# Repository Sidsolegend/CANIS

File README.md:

# CANIS

A small robot that gives my dog treats for calm behaviour.

*The current robot: a Meccano frame, an ESP32 and an Arduino on a breadboard, an ESP32-CAM on top, and three ultrasonic sensors at the front.*

## Why I built it

My Goldendoodle, Shifu, is afraid of moving objects. He also barks for attention, and he gets into trouble when he is bored. A robot is the worst possible thing to put in front of a dog like that, so the design starts from that constraint. CANIS never punishes him and never drives towards him. It rewards him when he settles, when he leaves a spot he shouldn't be in, or when he stops barking. Any motion is something I introduce slowly and switch off by default.

## What it does

- **Three modes.** `PLACE` (the default) gives a treat when Shifu settles on his mat. `GUARD` stays at a spot, gives a short buzzer cue when he comes near, and rewards him for leaving. `PLAY` wanders the room, gives a treat when it sees him, then backs away so he can follow. It never moves towards him.
- **Dog detection.** A YOLO11n model on a Raspberry Pi 5 finds the dog in the camera image and estimates his bearing and distance. The camera is either the Pi's own or an ESP32-CAM streaming over WiFi.
- **Bark detection.** A DJI Mic 3 connects to the Pi over Bluetooth. After a bark, the robot waits for five seconds of quiet and then drops a treat. A dead or muted microphone is treated as "not quiet", so a failure never rewards the wrong thing.
- **Treat dispenser.** A servo-driven gate on an Arduino Uno, with a short tone before each treat so the sound predicts food. There is a cooldown between treats and a daily cap.
- **Dashboard.** A Flask app on the Pi shows live state, keeps an event log and exports CSV files for the study.
- **Safety layer.** The Arduino stops the motors if it hasn't heard from the ESP32 for one second, so a crashed program or a loose wire ends with a stopped robot. A single exposure setting decides how much motion is allowed at all. It starts at zero.
- **Closed-loop drive.** The N20 motors have encoders (754 counts per wheel turn, about 0.18 mm per count). A per-wheel speed controller matches the two wheels, and a control-barrier-function safety filter sits between the controller and the motors: it only removes motion towards Shifu, never adds it, so the robot never closes inside a 60 cm comfort distance. Top speed is capped at 0.35 m/s. Both have been run on the robot.

## How it was built

| | |
|---|---|
|  | **1. Prototype.** The first rolling version: a Meccano frame, a Raspberry Pi 5, and geared motors with large wheels. It proved the vision and treat loop before I committed to a design. |
|  | **2. CAD, version 1.** A fully printable two-tier enclosure, modelled in OpenSCAD for a Bambu P1S. |
|  | **3. CAD, version 2.** A flap-gate dispenser and a shell that closes around the boards. |
|  | **4. CAD, version 3.** A reshaped shell, which I never finished as a full set of parts. |
|  | **5. CAD, version 4.** The last printable design, with the deck and shell checked for slicing. |
|  | **6. What I actually run.** I stopped printing the shell and went back to the metal frame. The dispenser housing is the main printed part. The old motors were replaced with small N20 encoder motors, and the front sensor, ESP32-CAM and bark detection were added. |

The longer story, including what went wrong, is in [docs/BUILD_STORY.md](docs/BUILD_STORY.md).

## Architecture

```mermaid
flowchart LR
    subgraph Pi["Raspberry Pi 5 (eyes, ears, dashboard)"]
        V["YOLO dog detection"]
        B["Bark detector (DJI Mic 3)"]
        D["Flask dashboard and event log"]
    end
    subgraph ESP["ESP32 (brain)"]
        S["Ultrasonic sensors"]
        M["State machine and reward policy"]
    end
    subgraph UNO["Arduino Uno (limbs)"]
        W["1 s motion watchdog"]
        MOT["L298N and motors"]
        G["Servo gate and buzzer"]
    end
    V --> D
    B --> D
    D <-- WiFi --> M
    S --> M
    M -- serial --> UNO
```

Each processor does one kind of job, and each one fails on its own. The Uno is deliberately simple. It runs the motors and the gate and stops the wheels when commands stop arriving. The ESP32 reads the sensors and decides what to do. The Pi does the heavy work (vision, audio, logging). More in [docs/ARCHITECTURE.md](docs/ARCHITECTURE.md) and [docs/TECHNICAL_OVERVIEW.md](docs/TECHNICAL_OVERVIEW.md).

## Hardware

| Part | Used for |
|---|---|
| Raspberry Pi 5 | vision, bark detection, dashboard |
| ESP32 DevKit V1 | sensors, state machine, WiFi |
| Arduino Uno | dispenser, motors, buzzer |
| ESP32-CAM (AI-Thinker, OV2640) | camera on the robot |
| L298N driver, 2 x GA12-N20 150 rpm encoder motors, 43 mm wheels | drive |
| 2 x HC-SR04 and 1 x JSN-SR04M-2 | left, right and front distance |
| SG90 servo, small buzzer | treat gate and the marker tone |
| DJI Mic 3 | bark detection, over Bluetooth |
| 6 x AA pack for the motors, a small USB power bank for the electronics | power |
| Meccano frame, printed dispenser housing, castor | chassis |

Wiring, pin tables and power notes: [hardware/WIRING.md](hardware/WIRING.md). Bring-up tests: [hardware/TESTING.md](hardware/TESTING.md).

## Repository layout

```
CANIS_Core/              ESP32 firmware (brain)
Treat_Dispenser_CANIS/   Arduino firmware (dispenser, motors, buzzer)
canis_config.h           every tunable value for the firmware, in one place
vision/                  YOLO dog detection (Pi)
audio/                   bark detection (Pi)
dashboard/               Flask dashboard and event log (Pi)
control/                 closed-loop controller and safety filter
study/                   study protocol and the analysis script
tests/                   118 tests, no hardware needed
hardware/                wiring, bring-up guides, CAD, STL files
docs/                    architecture, safety, interfaces, build story, known issues
prototypes/              early test sketches from before the current firmware
```

## Running it

Run the tests (no hardware needed):

```bash
pip install pytest numpy -r dashboard/requirements.txt
python3 -m pytest tests/ -q
```

Run the dashboard on the Pi:

```bash
cd dashboard
pip install -r requirements.txt
export CANIS_TOKEN=$(openssl rand -hex 16)   # shared secret, also set in arduino_secrets.h
python3 app.py                                # listens on port 5000
```

Flash the firmware: copy `CANIS_Core/arduino_secrets.h.example` to `CANIS_Core/arduino_secrets.h` and fill in your WiFi details, the Pi's address and the token. That file is git-ignored. Then flash `CANIS_Core` to the ESP32 (115200 baud) and `Treat_Dispenser_CANIS` to the Uno (9600 baud).

Start vision and bark detection on the Pi. Setup commands are at the top of each file.

```bash
python3 vision/detect_yolo.py --zone kitchen
python3 audio/detect_bark.py --bt-mac <microphone address>
```

## Status

What has been run:
- The full loop, camera to detection to dashboard to ESP32 to treat, works on the bench.
- The bark loop works end to end: a bark, five seconds of quiet, then a treat. In the live test there were no false positives.
- Encoder test: 754 counts per wheel turn, measured over 10 hand turns with 4x decoding. That fits a 3-pulse encoder on a 63:1 gearbox (3 x 63 x 4 = 756).
- Mobile drive with the closed-loop controller and the safety filter has been tested on the robot, with Shifu in the room.
- 118 automated tests pass.

The trial with Shifu:
- Week 1 was stationary acclimation: treats on, no motion, sessions growing from 15 to 60 minutes a day. He was scared of the robot the first time and got used to it over these sessions.
- Week 2 turned on mobile drive and `GUARD`. Over that week, treats earned rose by about 25% from day 1 to day 7.
- This is one dog with no control, so I can't rule out that he simply got used to the robot, and treats are counted when they are sent, not when they drop (see below). The raw session logs are in my notes, not in this repo yet.

Not finished yet:
- The repo config still has the old wheel values and `CANIS_MOBILE_ENABLED` set to 0. The robot runs with the measured values; the config here will be updated.
- Treat confirmation from the dispenser is designed but not wired (the 5 V to 3.3 V return line needs a divider), so treats are counted on send.
- The next step is a pre-registered study with a proper baseline, following [study/STUDY_PROTOCOL.md](study/STUDY_PROTOCOL.md).

Known problems and limits are listed in [docs/KNOWN_ISSUES.md](docs/KNOWN_ISSUES.md).

## About the code

I built and wired the robot, ran the bench tests and decided how it should behave around Shifu. AI coding assistants helped write and review parts of the software and the documentation.

## License

MIT. See [LICENSE](LICENSE).

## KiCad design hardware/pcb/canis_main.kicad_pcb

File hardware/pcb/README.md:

# CANIS main board (v1, untested)

One 100 x 90 mm, 2-layer, all through-hole board that replaces the Arduino Uno, the breadboard and the loose wiring. The L298N module stays off-board and is wired to it. The ESP32 DevKit plugs into two 1x15 sockets. Everything else is on the board.

Status: DRC clean (0 errors, 0 unconnected, only silkscreen-overlap warnings) in KiCad, and `check_netlist.py` passes. **Never fabricated or powered.** Treat the checklist below as required before ordering.

## What is on it

| Block | Parts | Notes |
|---|---|---|
| Logic | ATmega328P-PU in a DIP-28 socket, 16 MHz crystal, 2 x 22p, 10k reset, reset button | Same pins as the Uno, so `Treat_Dispenser_CANIS.ino` runs unchanged (D2 button, D3/D4/D7/D8/D12/D5 motors, D6 buzzer, D9 servo, D10/D11 link, A0 beam) |
| Motors | 1x6 header (ENA IN1 IN2 IN3 IN4 ENB, same order as the module's own header) and a 2-pin screw terminal (12V, GND) for your existing red L298N module | Use female-female jumpers for the 6 control wires. Motor wires go straight to the module's own OUT terminals. Leave the module's 5V jumper on; its 5V terminal is not connected to this board |
| Power | LM2596T-5.0 buck + 33uH + 1N5822 + 470u in/out, 1N5822 reverse-polarity diode on the battery | Battery in goes to the L298 (VMOT) and the buck. 1N5819 from 5V to ESP32 VIN so USB cannot back-feed the buck |
| Sensors | 3 x 4-pin (5V, TRIG, ECHO, GND) with 1k series on each ECHO, 2 x 4-pin encoder (3V3, GND, A, B) with 10k pull-ups, I2C header | Pin map is `canis_config.h` and the `.ino` files, not the old WIRING.md |
| Outputs | servo (3-pin), buzzer (2-pin with 220R), button (2-pin), beam (3-pin), ESP32-CAM 5V/GND | |
| Programming | ICSP 2x3, UART 4-pin (GND, DTR, TX, RX) with auto-reset cap | |
| Link | ESP32 GPIO13 to ATmega D10 direct; ATmega D11 to ESP32 GPIO4 through 1k + 2.2k divider | This is the dispense-ACK return line, so `CANIS_USE_DISPENSE_ACK` can be 1 on this board |

ESP32 pins: US trig/echo 27/25 (centre), 32/34 (left), 14/35 (right); encoders L 33/26, R 36/39; link 13 and 4; I2C 21/22.

## Before you order (check these)

1. **DevKit pinout and row spacing.** The board assumes a 30-pin DevKit V1 with rows 25.4 mm apart and USB at the top edge of the board. Measure yours with calipers (`ESP_AX`/`ESP_BX` in `gen_pcb.py`) and check the pin order against its silkscreen.
2. **L298N module header order.** The 6-pin control header is wired ENA, IN1, IN2, IN3, IN4, ENB, top to bottom as on the usual red module. Check yours against its silkscreen. Print `canis_main_testprint_1to1.pdf` at 100% and drop the real parts on it (LM2596, terminal blocks, crystal, DevKit) before paying for boards.
3. **LM2596 pinout** is the standard TO-220-5 (1 Vin, 2 Out, 3 GND, 4 FB, 5 ON/OFF to GND). Set nothing, it is the fixed 5.0 V part. Measure 5 V on the board with nothing plugged in before adding the ESP32 or the ATmega.
4. **Motor drop.** The L298N module still drops about 2 V, plus 0.4 V in the reverse diode, so the N20 motors see roughly 7 V from a 9.9 V pack. Same as the module today, minus the diode.
5. **Antenna.** There is a copper keep-out under the DevKit's antenna end. It does not fix the weak WiFi (-72 to -84 dBm in the notes).

## Bring-up order

1. Solder power only (J3, D1, C1, C3, U2, D2, L1, C2). Battery in, meter the 5V rail. Mind the polarity: the lower terminal of J3 is +.
2. Add the ATmega socket parts, crystal, caps, reset. The chip needs the Uno bootloader once: burn it over ICSP (a USBasp or another Uno as ISP), or buy it pre-flashed. After that the UART header uploads the sketch with auto-reset. Do not power the board from the programmer's 5V at the same time as the battery.
3. Add the headers and terminals, then wire the L298N module. Plug the DevKit in last.

GND pads are connected solid to the pour (thermal spokes kept landing on islands), so use a hot iron and flux.

## Files

- `gen_pcb.py` builds the board; `route.py` autoroutes with Freerouting (jar not in the repo, Java 21+) and pours GND; `build.sh` regenerates and renders.
- `check_netlist.py` re-checks the board's pins against the firmware sources (run it after any change).
- `canis_main.kicad_pcb`, `canis_main.kicad_pro`: open in KiCad. There is no schematic file; the netlist lives in `gen_pcb.py` (net names are the signal names above).
- `gerbers/` and `canis_main_gerbers.zip`: fab files (Gerber + Excellon).
- `canis_main_bom.csv`, `canis_main_preview.png`, `canis_main_testprint_1to1.pdf`.

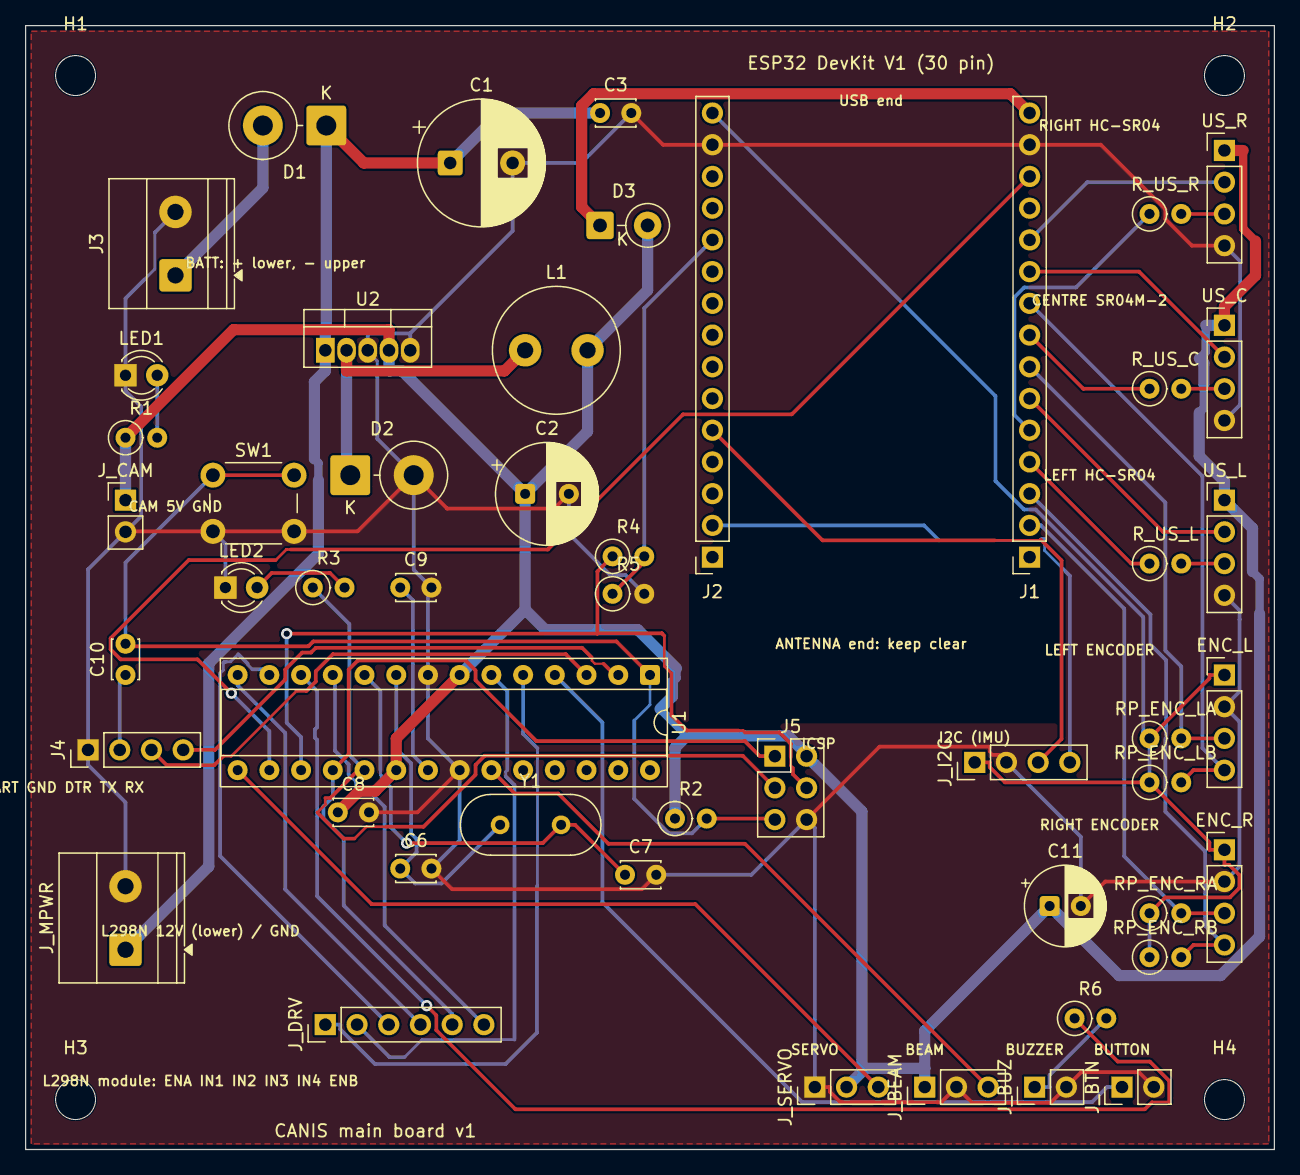
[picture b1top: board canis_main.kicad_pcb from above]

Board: 2 copper layers, 100.0 x 90.0 mm, 54 parts (0 on the bottom side), 46 nets.

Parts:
C1: 470u 25V; CP_Radial_D10.0mm_P5.00mm
C2: 470u 16V (5V out); CP_Radial_D8.0mm_P3.50mm
C3: 100n; C_Disc_D3.0mm_W2.0mm_P2.50mm
C6, C7: 22p; C_Disc_D3.0mm_W2.0mm_P2.50mm
C8: 100n VCC; C_Disc_D3.0mm_W2.0mm_P2.50mm
C9: 100n AREF; C_Disc_D3.0mm_W2.0mm_P2.50mm
C10: 100n DTR; C_Disc_D3.0mm_W2.0mm_P2.50mm
C11: 220u servo; CP_Radial_D6.3mm_P2.50mm
D1: 1N5822 reverse protect; D_DO-201AD_P5.08mm_Vertical_CathodeUp
D2: 1N5822 buck; D_DO-201AD_P5.08mm_Vertical_CathodeUp
D3: 1N5819 5V->VIN; D_DO-41_SOD81_P3.81mm_Vertical_CathodeUp
ENC_L: LEFT ENCODER 3V3 GND A B; PinHeader_1x04_P2.54mm_Vertical
ENC_R: RIGHT ENCODER 3V3 GND A B; PinHeader_1x04_P2.54mm_Vertical
H1, H2, H3, H4: M3; MountingHole_3.2mm_M3
J1: ESP32 DevKit left header (EN..VIN); PinSocket_1x15_P2.54mm_Vertical
J2: ESP32 DevKit right header (D23..3V3); PinSocket_1x15_P2.54mm_Vertical
J3: BATT 6xAA; TerminalBlock_Phoenix_MKDS-1,5-2-5.08_1x02_P5.08mm_Horizont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
J4: UART (FTDI/CP2102) GND DTR TXD RXD; PinHeader_1x04_P2.54mm_Vertical
J5: ICSP; PinHeader_2x03_P2.54mm_Vertical
J_BEAM: BEAM 5V GND OUT; PinHeader_1x03_P2.54mm_Vertical
J_BTN: BUTTON D2 GND; PinHeader_1x02_P2.54mm_Vertical
J_BUZ: BUZZER SIG GND; PinHeader_1x02_P2.54mm_Vertical
J_CAM: ESP32-CAM 5V GND; PinHeader_1x02_P2.54mm_Vertical
J_DRV: TO L298N module: ENA IN1 IN2 IN3 IN4 ENB; PinHeader_1x06_P2.54mm_Vertical
J_I2C: I2C 3V3 GND SDA SCL; PinHeader_1x04_P2.54mm_Vertical
J_MPWR: TO L298N 12V / GND; TerminalBlock_Phoenix_MKDS-1,5-2-5.08_1x02_P5.08mm_Horizont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
J_SERVO: SERVO GND 5V SIG; PinHeader_1x03_P2.54mm_Vertical
L1: 33uH 3A; L_Radial_D10.0mm_P5.00mm_Fastron_07P
LED1: green 5V; LED_D3.0mm
LED2: amber D13; LED_D3.0mm
R1, R3, R4: 1k; R_Axial_DIN0207_L6.3mm_D2.5mm_P2.54mm_Vertical
R2: 10k reset; R_Axial_DIN0207_L6.3mm_D2.5mm_P2.54mm_Vertical
R5: 2.2k; R_Axial_DIN0207_L6.3mm_D2.5mm_P2.54mm_Vertical
R6: 220; R_Axial_DIN0207_L6.3mm_D2.5mm_P2.54mm_Vertical
RP_ENC_LA: 10k; R_Axial_DIN0207_L6.3mm_D2.5mm_P2.54mm_Vertical
RP_ENC_LB: 10k; R_Axial_DIN0207_L6.3mm_D2.5mm_P2.54mm_Vertical
RP_ENC_RA: 10k; R_Axial_DIN0207_L6.3mm_D2.5mm_P2.54mm_Vertical
RP_ENC_RB: 10k; R_Axial_DIN0207_L6.3mm_D2.5mm_P2.54mm_Vertical
R_US_C: 1k; R_Axial_DIN0207_L6.3mm_D2.5mm_P2.54mm_Vertical
R_US_L: 1k; R_Axial_DIN0207_L6.3mm_D2.5mm_P2.54mm_Vertical
R_US_R: 1k; R_Axial_DIN0207_L6.3mm_D2.5mm_P2.54mm_Vertical
SW1: RESET; SW_PUSH_6mm
U1: ATmega328P-PU (Uno bootloader); DIP-28_W7.62mm_Socket
U2: LM2596T-5.0; TO-220-5_Vertical
US_C: CENTRE SR04M-2 5V TRIG ECHO GND; PinHeader_1x04_P2.54mm_Vertical
US_L: LEFT HC-SR04 5V TRIG ECHO GND; PinHeader_1x04_P2.54mm_Vertical
US_R: RIGHT HC-SR04 5V TRIG ECHO GND; PinHeader_1x04_P2.54mm_Vertical
Y1: 16 MHz; Crystal_HC49-4H_Vertical

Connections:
3V3: ENC_L.1, ENC_R.1, J2.15, J_I2C.1, RP_ENC_LA.1, RP_ENC_LB.1, RP_ENC_RA.1, RP_ENC_RB.1
5V: C2.1, C8.1, C11.1, D3.2, J5.2, J_BEAM.1, J_CAM.1, J_SERVO.2, L1.2, R1.1, R2.1, U1.7, U1.20, U2.4, US_C.1, US_L.1, US_R.1
AREF: C9.1, U1.21
BEAM: J_BEAM.3, U1.23
BTN: J_BTN.1, U1.4
BUZ: J_BUZ.1, R6.2
BUZ_RAW: R6.1, U1.12
D0_RX: J4.4, U1.2
D1_TX: J4.3, U1.3
D13_LED: J5.3, R3.1, U1.19
DTR: C10.1, J4.2
ENC_L_A: ENC_L.3, J1.7, RP_ENC_LA.2
ENC_L_B: ENC_L.4, J1.9, RP_ENC_LB.2
ENC_R_A: ENC_R.3, J1.2, RP_ENC_RA.2
ENC_R_B: ENC_R.4, J1.3, RP_ENC_RB.2
GND: C1.2, C2.2, C3.2, C6.2, C7.2, C8.2, C9.2, C11.2, D2.2, ENC_L.2, ENC_R.2, J1.14, J2.14, J3.2, J4.1, J5.6, J_BEAM.2, J_BTN.2, J_BUZ.2, J_CAM.2, J_I2C.2, J_MPWR.2, J_SERVO.1, LED1.1, LED2.1, R5.2, SW1.2, U1.8, U1.22, U2.3, U2.5, US_C.4, US_L.4, US_R.4
I2C_SCL: J2.2, J_I2C.4
I2C_SDA: J2.5, J_I2C.3
LED5: LED1.2, R1.2
LED13: LED2.2, R3.2
LINK_RX_AT: J1.13, U1.16
LINK_TX_AT: J5.4, R4.1, U1.17
LINK_TX_DIV: J2.11, R4.2, R5.1
M_ENA: J_DRV.1, U1.5
M_ENB: J_DRV.6, U1.11
M_IN1: J_DRV.2, U1.6
M_IN2: J_DRV.3, U1.13
M_IN3: J_DRV.4, U1.14
M_IN4: J5.1, J_DRV.5, U1.18
RESET: C10.2, J5.5, R2.2, SW1.1, U1.1
SERVO: J_SERVO.3, U1.15
SW: D2.1, L1.1, U2.2
US_C_ECHO: J1.8, R_US_C.1
US_C_ECHO_RAW: R_US_C.2, US_C.3
US_C_TRIG: J1.10, US_C.2
US_L_ECHO: J1.4, R_US_L.1
US_L_ECHO_RAW: R_US_L.2, US_L.3
US_L_TRIG: J1.6, US_L.2
US_R_ECHO: J1.5, R_US_R.1
US_R_ECHO_RAW: R_US_R.2, US_R.3
US_R_TRIG: J1.11, US_R.2
VBAT: D1.2, J3.1
VIN_ESP: D3.1, J1.15
VMOT: C1.1, C3.1, D1.1, J_MPWR.1, U2.1
XTAL1: C6.1, U1.9, Y1.1
XTAL2: C7.1, U1.10, Y1.2

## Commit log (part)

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2026-06-25 Initial commit: CANIS conditioning robot
    Working closed loop: sensors -> state machine -> dispense + buzzer cue,
    with live ESP32->Pi dashboard. Credentials kept out of git via
    arduino_secrets.h (gitignored).
    Subsystems:
    - CANIS_Core: integrated ESP32 brain (PIR + ultrasonic, arousal state
    machine, treat dispense, CORRECTION buzzer cue, reward cooldown/cap,
2026-06-25 Docs: update setup for arduino_secrets.h credential flow
2026-06-25 Add systemd service for the dashboard; make Flask debug opt-in (CANIS_DEBUG)
2026-06-25 Docs: Pi prepped for vision (opencv-contrib + ArUco); dashboard auto-start
2026-06-25 Add Pi->ESP32 vision command channel (/detect, /command) + ArUco detection script
    - Flask: /detect (vision posts zone) + /command (ESP32 polls); TTL-based staleness
    - CANIS_Core: polls /command, folds vision detections into arousal drive, shares Pi back-off
    - vision/detect.py: ArUco marker detection -> POST zone, with --test mode (no camera needed)
    - docs: refreshed repo layout + Phase 6 status
2026-06-25 Harden CANIS_Core: fixed-buffer visionZone (no heap churn) + rollover-safe backoff
2026-06-25 Reward tuning: gate sustained-calm reward until warm-up; calm interval (30s) >= cooldown (20s)
2026-06-25 Add hardware/WIRING.md (pinout + power architecture + L298N plan); refresh README
    - New hardware/WIRING.md: every pin, the ECHO protection, power architecture
    (USB now, battery/buck later), and the planned L298N->Arduino wiring
    - README: rate-driven arousal description (was stale +25 bump), CANIS_Core as
    the main sketch, hardware/power links, refreshed phase status
2026-06-29 Add parametric 3D-printed chassis, product shell & mounts (hardware/cad)
    Parametric OpenSCAD model (canis.scad) for the hybrid CANIS build, sized for
    a Bambu P1S in PLA. Seven printable parts + STLs + preview renders.
    - Deck (230x175): ribbed load-bearing plate with a real, collision-free home for
    every component — Pi 5 cradle, board pads (Arduino, ESP32, L298N, LM2596 buck),
    breadboard pad, dispenser/motor/castor/shell holes, cable routing.
    - Shell: product enclosure with a "paw" front that actually mounts the sensors
2026-06-29 Fix layout overlaps: re-pack deck (240x185), separate servo tower, relocate shell bosses
    - Deck 230x175 -> 240x185; re-pack so NO pad/cradle/dispenser/boss overlaps.
    Breadboard pad no longer intersects the Pi cradle.
    - Dispenser: servo tower moved BEHIND the throat with an asymmetric base, so it
    no longer cuts into the funnel/throat; shell hopper opening is now an oval that
    clears funnel + tower.
    - Shell screw bosses relocated to verified-clear perimeter gaps (were landing
2026-06-29 Fix deck ribs through throat, declutter paw mounts, clean dispenser; deck 248x190
    Geometry bugs caught by per-part close-up renders:
    - Deck: a stiffening rib ran under the throat (would block treats). Ribs moved
    clear of the throat AND all holes/slots now cut FULL depth (through ribs), so
    the throat, cable slots and screw holes are never blocked.
    - Deck mounts: boards on 4 open standoffs (deck stays open underneath), breadboard
    on a perimeter lip (open centre) — nothing covers the deck or its holes.
2026-06-29 Rebuild as clean two-tier model (205x165): lower deck + upper shelf, modular sensor plate
    Fresh rebuild after the single-tier file accumulated geometry bugs. Simpler,
    smaller, verified part-by-part:
    - Two tiers: lower deck (Pi 5, L298N, buck, motors, castor, dispenser) + upper
    shelf on 4 standoffs (Arduino, breadboard, ESP32). Shelf has a rear notch so
    the dispenser funnel passes up through it.
    - No underside ribs (4mm plate + skirt) -> nothing crosses the throat/holes.
2026-06-29 Clean funnel + separate servo bracket, readable logo, single combined STL
    - Dispenser is now a CLEAN funnel only (round throat + 3 feet); the servo moved
    to its own `servo_bracket` part beside the funnel, enclosed under the shell.
    No more tab/notch fighting the throat.
    - Shell hopper opening simplified to the funnel circle; CANIS logo deepened so
    it's clearly readable on the rear.
    - Shelf wire holes tidied into a clean column.
2026-06-29 Push CANIS logo down clear of the hopper opening (now fully readable)
2026-06-29 Rebuild dispenser as a working rotating-disc mechanism (servo + disc + chute)
    Replaces the non-functional funnel+gate. Now an actual mechanism:
    - dispenser = round housing + funnel; the SG90 stands upright INSIDE (shaft up),
    the disc sits on its shaft.
    - disc = one metering pocket + centre horn socket; fills under the funnel inlet
    (-x), rotates 180deg, drops one kibble through the +x exit.
    - exit drops through the deck into the chute (under the deck) -> out at floor level.
2026-06-29 README: fix print-settings row (gate -> disc/chute) after dispenser rebuild
2026-06-29 Fix dispenser/chute mounting alignment (verification follow-up)
    - Dispenser feet moved inward (radius 29 -> 22) so they land in solid housing
    wall instead of half in air; deck holes follow (shared disp_pins).
    - Chute redesigned with a flat mounting flange + 2 holes; deck now has matching
    chute screw holes (shared chute_mt spacing).
    - Removed dead throat_d reference in the deck (unknown-variable warning).
    Chassis/shelf/sensor/castor/motor alignments unchanged; full assembly verified.
2026-06-29 Add BUILD_GUIDE.md (BOM, PLA print settings, step-by-step assembly); refresh all STLs
    - New hardware/cad/BUILD_GUIDE.md: parts list, per-part PLA print settings
    (orientation/supports/walls/infill), bill of materials + fasteners, and a
    step-by-step assembly walkthrough (where each board/part goes + which screws),
    plus how the rotating-disc dispenser works and the confirm-for-your-hardware list.
    - Re-exported all 9 individual STLs fresh.
    - Linked the guide from the README.
2026-06-29 Fix chute: continuous channel (vertical entry -> bend) removes the inlet lip/gap
2026-06-29 Chute: single smooth channel (remove the tube-in-tube internal step)
2026-06-29 Add original build reference photos (metal-chassis prototype)
2026-06-30 Add L298N motor firmware, 3-ultrasonic sensing, Pi-camera vision, test/setup docs
    - Treat_Dispenser_CANIS: L298N differential drive (FWD/BACK/LEFT/RIGHT/STOP)
    with a fail-safe motion watchdog; stop motors at dispense start
    - CANIS_Core: real CORRECTION orient (pulsed, EXPOSURE_LEVEL-gated, watchdog-fed);
    3 ultrasonics (L/C/R) read sequentially with local-bearing steering;
    freed GPIO14 by setting Serial2 RX to -1
    - Sensors_Test: standalone bench test for PIR + 3 ultrasonics
2026-06-30 Add print-ready v2 CAD: flap-gate dispenser, fit/labels, angled 3-ultrasonic shell
    Duplicate of canis.scad (canis_v2.scad) — originals untouched. STLs in stl_v2/,
    renders in preview_v2/, BUILD_GUIDE_v2.md.
    - Dispenser: rotating disc -> FLAP GATE (servo swings a paddle ~80deg off a gate
    hole). Matches the tested firmware (OPEN=0/CLOSED=80) -> no firmware change.
    - Deck: every component fits; added a 4xAA cradle [5], under-deck power-bank strap
    mount [6], wire-routing slots, and engraved number labels [1-6].
2026-06-30 Add modern-angular shell variant (canis_v3.scad)
    New duplicate; canis_v2.scad + originals untouched. Only the shell changed —
    all internals (deck, dispenser, sensors, numbered labels) identical to v2.
    - Shell: bulbous dome -> low faceted slab (crisp vertical sides, 45deg chamfered
    top edge, rear-biased flat top). Recessed front sensor-face panel
    (camera + SR04M-2 + PIR); 2x HC-SR04 on angled front-corner bores.
    - Funnel opening + fan grille on top; CANIS deboss on the rear face.
